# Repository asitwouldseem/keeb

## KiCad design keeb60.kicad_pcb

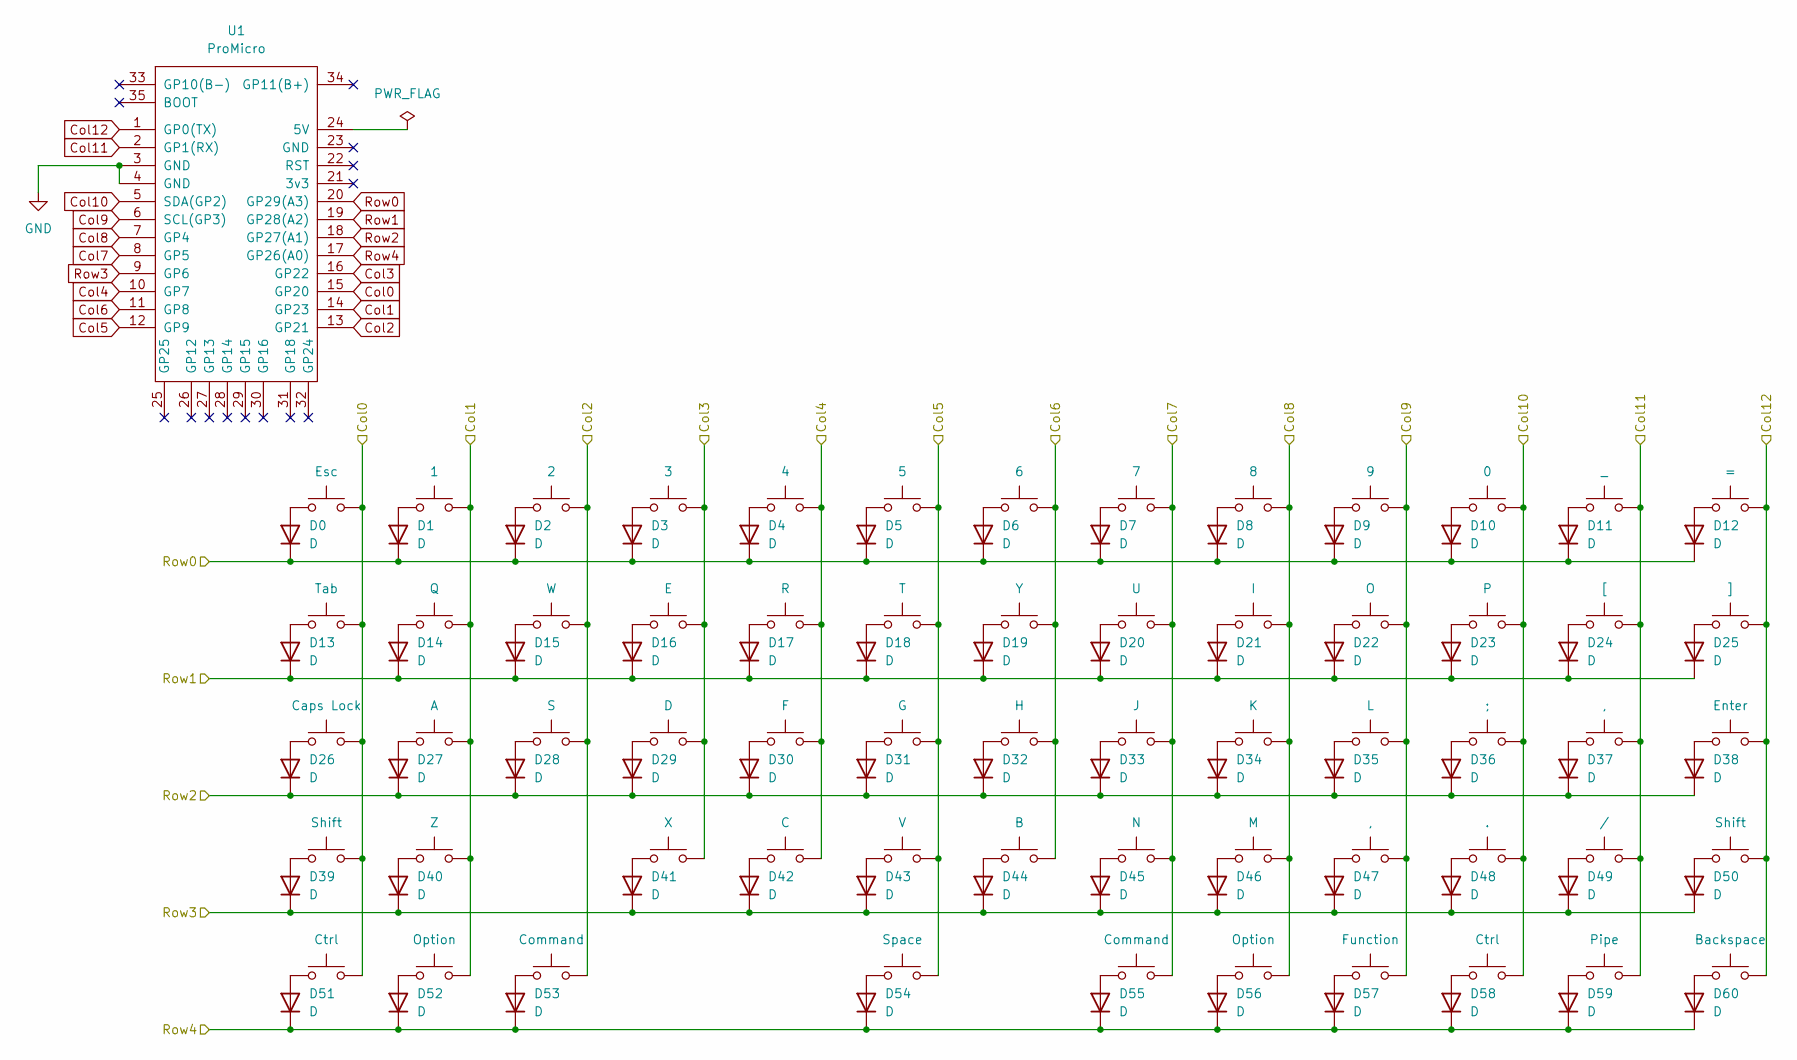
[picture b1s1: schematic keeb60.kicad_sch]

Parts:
D0, D1, D2, D3, D4, D5, D6, D7, D8, D9, D10, D11, D12, D13, D14, D15, D16, D17, D18, D19, D20, D21, D22, D23, D24, D25, D26, D27, D28, D29, D30, D31, D32, D33, D34, D35, D36, D37, D38, D39, D40, D41, D42, D43, D44, D45, D46, D47, D48, D49, D50, D51, D52, D53, D54, D55, D56, D57, D58, D59, D60: D; D_SOD-123
K000: Esc; MX-Hotswap-1U
K001: 1; MX-Hotswap-1U
K002: 2; MX-Hotswap-1U
K003: 3; MX-Hotswap-1U
K004: 4; MX-Hotswap-1U
K005: 5; MX-Hotswap-1U
K006: 6; MX-Hotswap-1U
K007: 7; MX-Hotswap-1U
K008: 8; MX-Hotswap-1U
K009: 9; MX-Hotswap-1U
K010: 0; MX-Hotswap-1U
K011: _; MX-Hotswap-1U
K012: =; MX-Hotswap-1U
K013: Backspace; MX-Hotswap-2U
K100: Tab; MX-Hotswap-1.5U
K101: Q; MX-Hotswap-1U
K102: W; MX-Hotswap-1U
K103: E; MX-Hotswap-1U
K104: R; MX-Hotswap-1U
K105: T; MX-Hotswap-1U
K106: Y; MX-Hotswap-1U
K107: U; MX-Hotswap-1U
K108: I; MX-Hotswap-1U
K109: O; MX-Hotswap-1U
K110: P; MX-Hotswap-1U
K111: [; MX-Hotswap-1U
K112: ]; MX-Hotswap-1U
K113: Pipe; MX-Hotswap-1.5U
K200: Caps Lock; MX-Hotswap-1.75U
K201: A; MX-Hotswap-1U
K202: S; MX-Hotswap-1U
K203: D; MX-Hotswap-1U
K204: F; MX-Hotswap-1U
K205: G; MX-Hotswap-1U
K206: H; MX-Hotswap-1U
K207: J; MX-Hotswap-1U
K208: K; MX-Hotswap-1U
K209: L; MX-Hotswap-1U
K210: ;; MX-Hotswap-1U
K211, K309: ,; MX-Hotswap-1U
K213: Enter; MX-Hotswap-2.25U
K300: Shift; MX-Hotswap-2.25U
K302: Z; MX-Hotswap-1U
K303: X; MX-Hotswap-1U
K304: C; MX-Hotswap-1U
K305: V; MX-Hotswap-1U
K306: B; MX-Hotswap-1U
K307: N; MX-Hotswap-1U
K308: M; MX-Hotswap-1U
K310: .; MX-Hotswap-1U
K311: /; MX-Hotswap-1U
K313: Shift; MX-Hotswap-2.75U
K400, K413: Ctrl; MX-Hotswap-1.25U
K401, K411: Option; MX-Hotswap-1.25U
K402, K410: Command; MX-Hotswap-1.25U
K406: Space; MX-Hotswap-6.25U-ReversedStabilizers
K412: Function; MX-Hotswap-1.25U
U1: ProMicro; TheOneProMicro

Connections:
Col0: K000.2, K100.2, K200.2, K300.2, K400.2, U1.15 (GP20)
Col1: K001.2, K101.2, K201.2, K302.2, K401.2, U1.14 (GP23)
Col2: K002.2, K102.2, K202.2, K402.2, U1.13 (GP21)
Col3: K003.2, K103.2, K203.2, K303.2, U1.16 (GP22)
Col4: K004.2, K104.2, K204.2, K304.2, U1.10 (GP7)
Col5: K005.2, K105.2, K205.2, K305.2, K406.2, U1.12 (GP9)
Col6: K006.2, K106.2, K206.2, K306.2, U1.11 (GP8)
Col7: K007.2, K107.2, K207.2, K307.2, K410.2, U1.8 (GP5)
Col8: K008.2, K108.2, K208.2, K308.2, K411.2, U1.7 (GP4)
Col9: K009.2, K109.2, K209.2, K309.2, K412.2, U1.6 (SCL(GP3))
Col10: K010.2, K110.2, K210.2, K310.2, K413.2, U1.5 (SDA(GP2))
Col11: K011.2, K111.2, K113.2, K211.2, K311.2, U1.2 (GP1(RX))
Col12: K012.2, K013.2, K112.2, K213.2, K313.2, U1.1 (GP0(TX))
GND: U1.3 (GND), U1.4 (GND)
unnamed: D0.2 (A), K000.1
unnamed: D1.2 (A), K001.1
unnamed: D2.2 (A), K002.1
unnamed: D3.2 (A), K003.1
unnamed: D4.2 (A), K004.1
unnamed: D5.2 (A), K005.1
unnamed: D6.2 (A), K006.1
unnamed: D7.2 (A), K007.1
unnamed: D8.2 (A), K008.1
unnamed: D9.2 (A), K009.1
unnamed: D10.2 (A), K010.1
unnamed: D11.2 (A), K011.1
unnamed: D12.2 (A), K012.1
unnamed: D13.2 (A), K100.1
unnamed: D14.2 (A), K101.1
unnamed: D15.2 (A), K102.1
unnamed: D16.2 (A), K103.1
unnamed: D17.2 (A), K104.1
unnamed: D18.2 (A), K105.1
unnamed: D19.2 (A), K106.1
unnamed: D20.2 (A), K107.1
unnamed: D21.2 (A), K108.1
unnamed: D22.2 (A), K109.1
unnamed: D23.2 (A), K110.1
unnamed: D24.2 (A), K111.1
unnamed: D25.2 (A), K112.1
unnamed: D26.2 (A), K200.1
unnamed: D27.2 (A), K201.1
unnamed: D28.2 (A), K202.1
unnamed: D29.2 (A), K203.1
unnamed: D30.2 (A), K204.1
unnamed: D31.2 (A), K205.1
unnamed: D32.2 (A), K206.1
unnamed: D33.2 (A), K207.1
unnamed: D34.2 (A), K208.1
unnamed: D35.2 (A), K209.1
unnamed: D36.2 (A), K210.1
unnamed: D37.2 (A), K211.1
unnamed: D38.2 (A), K213.1
unnamed: D39.2 (A), K300.1
unnamed: D40.2 (A), K302.1
unnamed: D41.2 (A), K303.1
unnamed: D42.2 (A), K304.1
unnamed: D43.2 (A), K305.1
unnamed: D44.2 (A), K306.1
unnamed: D45.2 (A), K307.1
unnamed: D46.2 (A), K308.1
unnamed: D47.2 (A), K309.1
unnamed: D48.2 (A), K310.1
unnamed: D49.2 (A), K311.1
unnamed: D50.2 (A), K313.1
unnamed: D51.2 (A), K400.1
unnamed: D52.2 (A), K401.1
unnamed: D53.2 (A), K402.1
unnamed: D54.2 (A), K406.1
unnamed: D55.2 (A), K410.1
unnamed: D56.2 (A), K411.1
unnamed: D57.2 (A), K412.1
unnamed: D58.2 (A), K413.1
unnamed: D59.2 (A), K113.1
unnamed: D60.2 (A), K013.1
Row0: D0.1 (K), D1.1 (K), D2.1 (K), D3.1 (K), D4.1 (K), D5.1 (K), D6.1 (K), D7.1 (K), D8.1 (K), D9.1 (K), D10.1 (K), D11.1 (K), D12.1 (K), U1.20 (GP29(A3))
Row1: D13.1 (K), D14.1 (K), D15.1 (K), D16.1 (K), D17.1 (K), D18.1 (K), D19.1 (K), D20.1 (K), D21.1 (K), D22.1 (K), D23.1 (K), D24.1 (K), D25.1 (K), U1.19 (GP28(A2))
Row2: D26.1 (K), D27.1 (K), D28.1 (K), D29.1 (K), D30.1 (K), D31.1 (K), D32.1 (K), D33.1 (K), D34.1 (K), D35.1 (K), D36.1 (K), D37.1 (K), D38.1 (K), U1.18 (GP27(A1))
Row3: D39.1 (K), D40.1 (K), D41.1 (K), D42.1 (K), D43.1 (K), D44.1 (K), D45.1 (K), D46.1 (K), D47.1 (K), D48.1 (K), D49.1 (K), D50.1 (K), U1.9 (GP6)
Row4: D51.1 (K), D52.1 (K), D53.1 (K), D54.1 (K), D55.1 (K), D56.1 (K), D57.1 (K), D58.1 (K), D59.1 (K), D60.1 (K), U1.17 (GP26(A0))

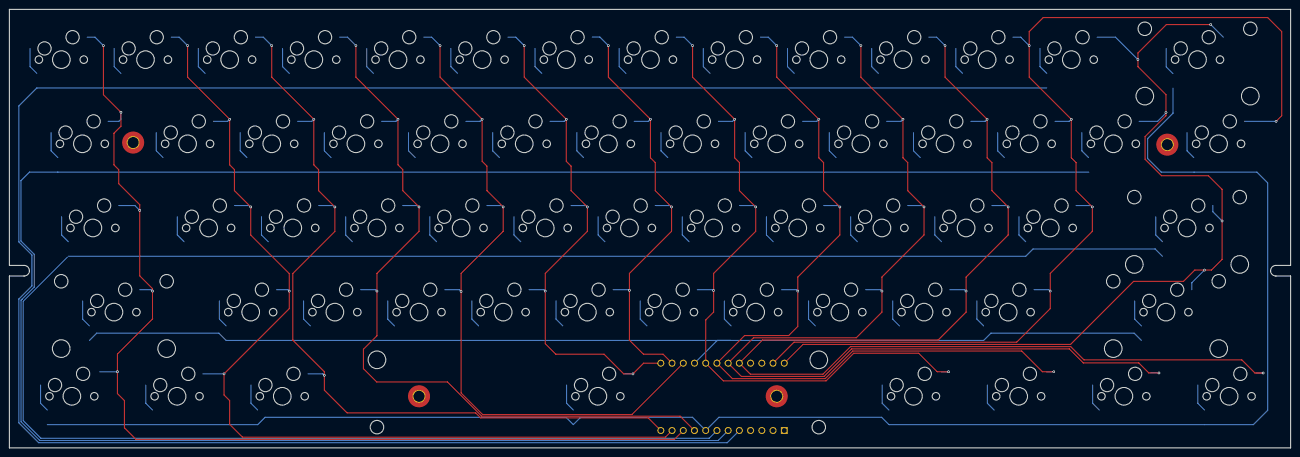
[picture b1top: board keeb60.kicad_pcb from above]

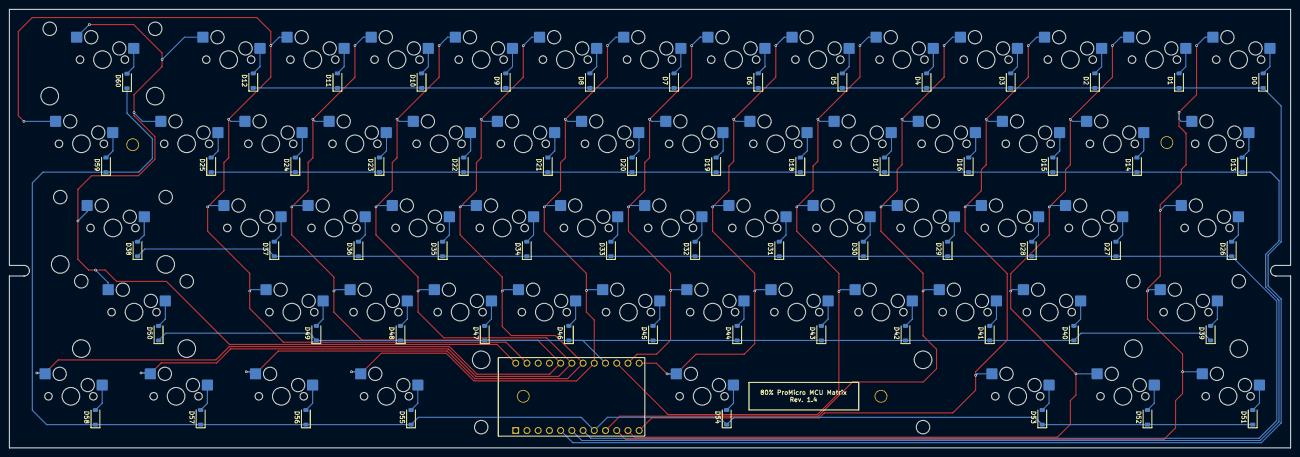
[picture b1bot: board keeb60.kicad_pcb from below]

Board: 2 copper layers, 290.0 x 99.2 mm, 123 parts (123 on the bottom side), 80 nets.

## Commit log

2025-09-21 Create project
2025-09-21 Add libraries
2025-09-21 Add power lines
2025-09-21 Add matrix
2025-09-22 Start assigning footprints
2025-09-22 Add footprints
2025-09-27 Switch to SMA diodes, start laying out board
2025-09-28 Start placing diodes
2025-09-28 All diodes positioned
2025-09-28 Move diodes to correct layers
2025-10-03 Remove JST from board
2025-11-02 Move to 13 columns
2025-11-02 Fix alignment, bah!
2025-11-02 Position diodes
2025-11-02 Add edge cut
2025-11-02 thangs
2025-11-02 Fix diodes
2025-11-02 More routing
2025-11-02 ROUTING!
2025-11-02 ROUTES BBY
2025-11-03 Start routing cols
2025-11-03 ~~magic~~
2025-11-03 more!
2025-11-05 Route rows
2025-11-05 Tidy
2025-11-05 Finish routing cols
2025-11-08 Fix track widths
2025-11-08 Tidy tidy
2025-11-08 Oops, move to B.Cu
2025-11-08 Enough for tonight
2025-11-09 Fix col routing
2025-11-11 Columns V2
2025-11-11 V1.2
2025-11-11 Post-DRC V1.2
2025-11-11 Add mounting holes to match plate
2025-11-12 Arcs rather than circles
2025-11-12 Import edge.cuts
2025-11-12 Fix DRC. V1.3
2025-11-12 Add silkscreen
2025-11-13 Add ground zone
2025-11-13 Set all pads to top only
2025-11-13 Start moving vias to be adjacent to pads
2025-11-13 More via tweaks
2025-11-14 One row left!
2025-11-14 Tweak top row
2025-11-14 Backspace tweaks
2025-11-14 Fix vias on final row
2025-11-14 Move to v1.4
2025-11-14 Extra padding for traces for JLCPCB
2025-11-14 Update silkscreen for JLCPCB DRC
2025-11-14 Move vias near mounting holes for JLCPCB DRC
2025-11-14 Change footprint silkscreen to 1.5 for DRC
2025-11-15 Flip nicenano for USB-C access
2025-11-15 DFM tweak
2025-12-22 Change stabs
